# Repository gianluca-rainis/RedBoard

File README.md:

# Redboard
Design an RP2040-powered board, get funds to build it!

## What is Readboard
Redboard is a YSWS where students design a custom RP2040-powered PCB from scratch, earn credits based on tracked hours, and redeem them for grants to manufacture and build their board.

## How does it works
For each project there will be two phases: 
- The design phase, where participants design any RP2040-powered board, develop the PCB and track their time spent on KiCad with Lapse. After shipping the project, they will receive 1 credit per hour tracked. 
- The build phase, where participants spend their credits in the shop to get: a PCB manufacturing grant; a components grant; optional tools (soldering iron, multimeter, etc.). Then they physically build the board, tracking the build time with Lapse and earning additional credits.

## What a shipped project will have
A shipped Phase 1 project includes:
- Public GitHub repo with all the source files
- Handwritten README and JOURNEY files
- Photos of the board design

A shipped Phase 2 project includes:
- A short video of the board working
- Photos of the assembled board

## Colors
#c01749
#d42060
#e01f5a

## Env file content
> SITE_URL

The url of the site

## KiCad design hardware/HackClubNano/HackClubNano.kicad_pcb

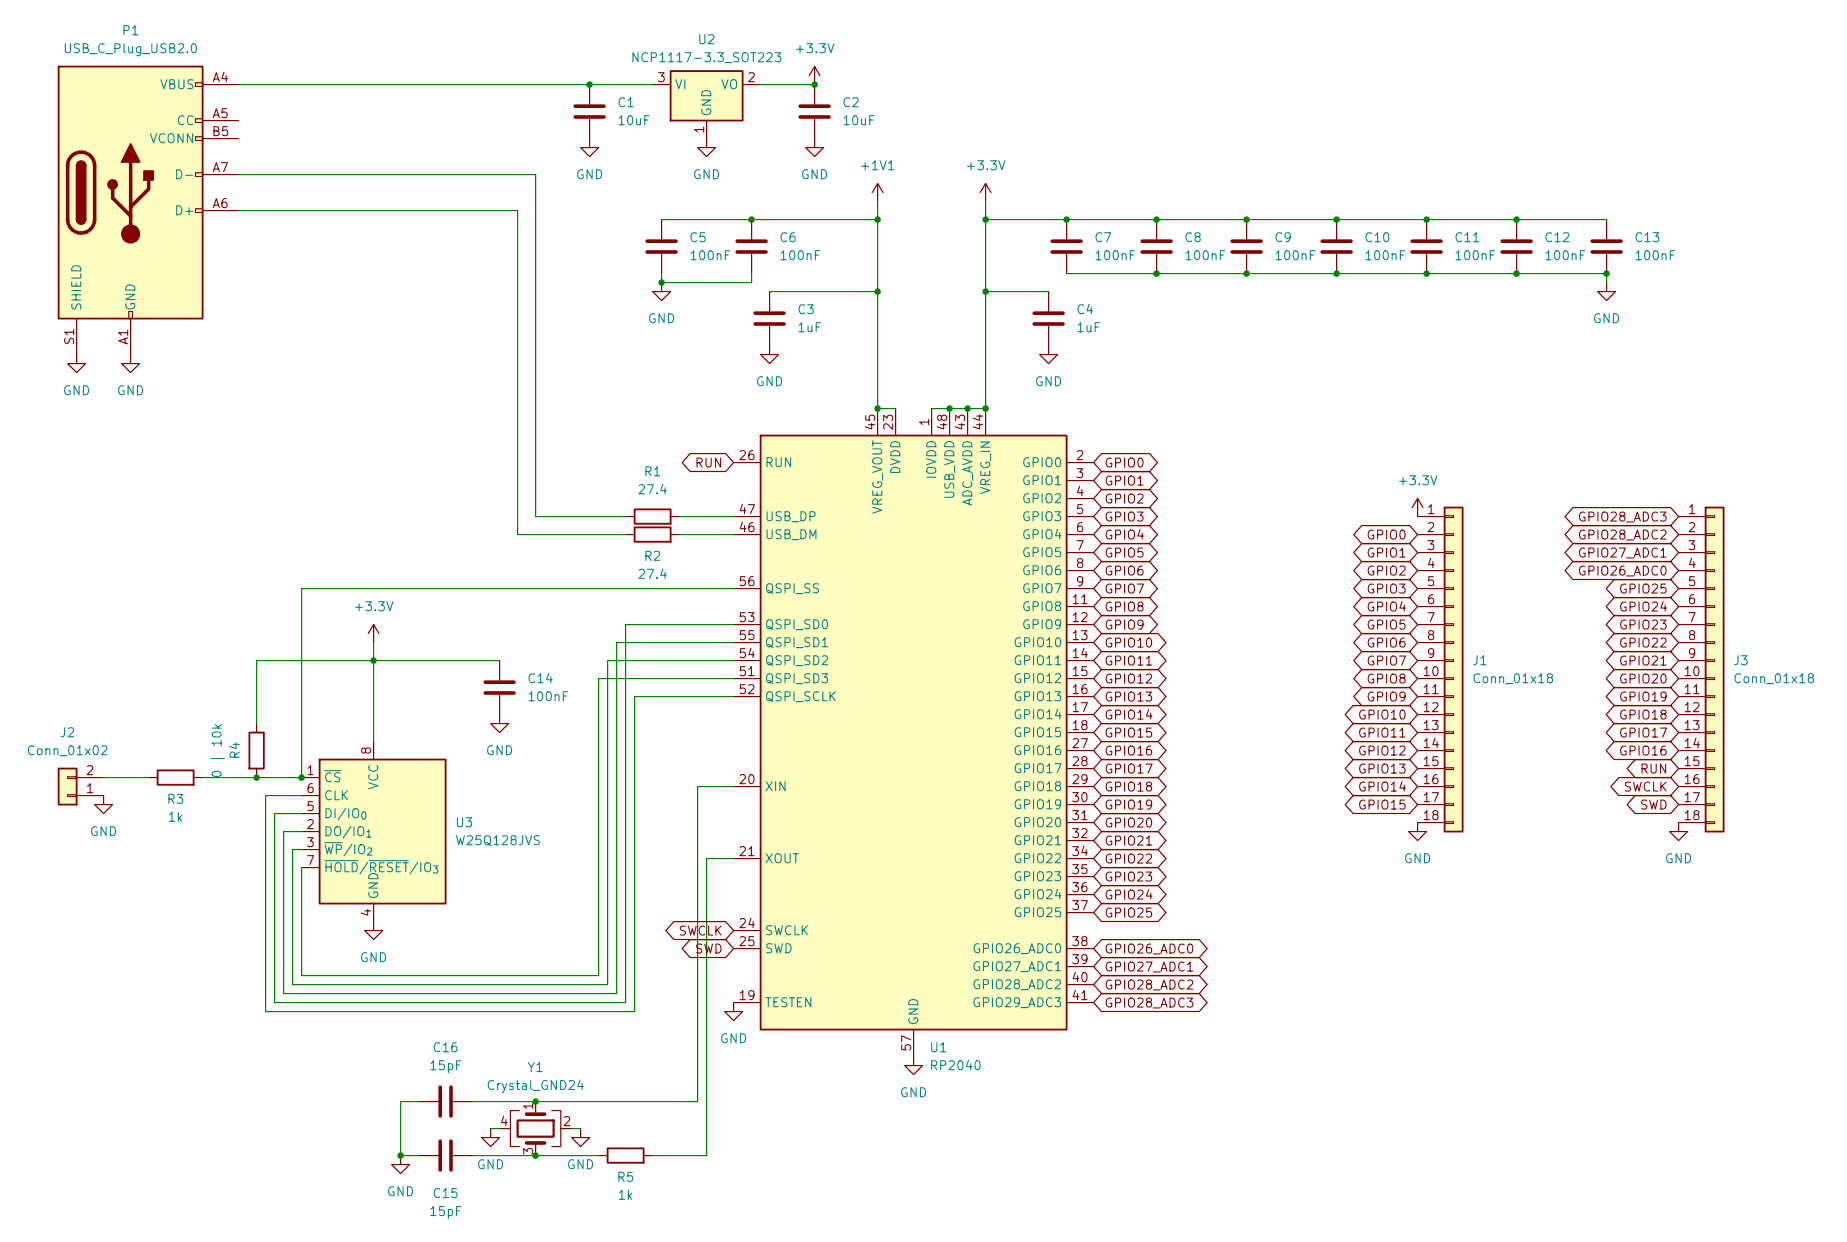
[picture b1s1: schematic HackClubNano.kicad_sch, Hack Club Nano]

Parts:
C1, C2: 10uF; C_0603_1608Metric
C3, C4: 1uF; C_0603_1608Metric
C5, C6, C7, C8, C9, C10, C11, C12, C13, C14: 100nF; C_0603_1608Metric
C15, C16: 15pF; C_0603_1608Metric
J1, J3: Conn_01x18; PinHeader_1x18_P2.00mm_Vertical
J2: Conn_01x02; PinHeader_1x02_P2.00mm_Vertical
P1: USB_C_Plug_USB2.0; USB_C_Receptacle_HRO_TYPE-C-31-M-12
R1, R2: 27.4; R_Axial_DIN0207_L6.3mm_D2.5mm_P7.62mm_Horizontal
R3, R5: 1k; R_Axial_DIN0207_L6.3mm_D2.5mm_P7.62mm_Horizontal
R4: 0 | 10k; R_Axial_DIN0207_L6.3mm_D2.5mm_P7.62mm_Horizontal
U1: RP2040; QFN-56-1EP_7x7mm_P0.4mm_EP3.2x3.2mm
U2: NCP1117-3.3_SOT223; SOT-223-3_TabPin2
U3: W25Q128JVS; SOIC-8_5.3x5.3mm_P1.27mm
Y1: Crystal_GND24; Crystal_SMD_5032-4Pin_5.0x3.2mm

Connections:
+1V1: C3.1, C5.1, C6.1, U1.23 (DVDD), U1.45 (VREG_VOUT), U1.50 (DVDD); also elsewhere on the board
+3.3V: C2.1, C4.1, C7.1, C8.1, C9.1, C10.1, C11.1, C12.1, C13.1, C14.1, J1.1, R4.1, U1.1 (IOVDD), U1.10 (IOVDD), U1.22 (IOVDD), U1.33 (IOVDD), U1.42 (IOVDD), U1.43 (ADC_AVDD), U1.44 (VREG_IN), U1.48 (USB_VDD), U1.49 (IOVDD), U2.2 (VO), U3.8 (VCC); also elsewhere on the board
GND: C1.2, C2.2, C3.2, C4.2, C5.2, C6.2, C7.2, C8.2, C9.2, C10.2, C11.2, C12.2, C13.2, C14.2, C15.2, C16.1, J1.18, J2.1, J3.18, P1.A1 (GND), P1.A12 (GND), P1.B1 (GND), P1.B12 (GND), P1.S1 (SHIELD), U1.19 (TESTEN), U1.57 (GND), U2.1 (GND), U3.4 (GND), Y1.2, Y1.4; also elsewhere on the board
GPIO0: J1.2, U1.2 (GPIO0); also elsewhere on the board
GPIO1: J1.3, U1.3 (GPIO1); also elsewhere on the board
GPIO2: J1.4, U1.4 (GPIO2); also elsewhere on the board
GPIO3: J1.5, U1.5 (GPIO3); also elsewhere on the board
GPIO4: J1.6, U1.6 (GPIO4); also elsewhere on the board
GPIO5: J1.7, U1.7 (GPIO5); also elsewhere on the board
GPIO6: J1.8, U1.8 (GPIO6); also elsewhere on the board
GPIO7: J1.9, U1.9 (GPIO7); also elsewhere on the board
GPIO8: J1.10, U1.11 (GPIO8); also elsewhere on the board
GPIO9: J1.11, U1.12 (GPIO9); also elsewhere on the board
GPIO10: J1.12, U1.13 (GPIO10); also elsewhere on the board
GPIO11: J1.13, U1.14 (GPIO11); also elsewhere on the board
GPIO12: J1.14, U1.15 (GPIO12); also elsewhere on the board
GPIO13: J1.15, U1.16 (GPIO13); also elsewhere on the board
GPIO14: J1.16, U1.17 (GPIO14); also elsewhere on the board
GPIO15: J1.17, U1.18 (GPIO15); also elsewhere on the board
GPIO16: J3.14, U1.27 (GPIO16); also elsewhere on the board
GPIO17: J3.13, U1.28 (GPIO17); also elsewhere on the board
GPIO18: J3.12, U1.29 (GPIO18); also elsewhere on the board
GPIO19: J3.11, U1.30 (GPIO19); also elsewhere on the board
GPIO20: J3.10, U1.31 (GPIO20); also elsewhere on the board
GPIO21: J3.9, U1.32 (GPIO21); also elsewhere on the board
GPIO22: J3.8, U1.34 (GPIO22); also elsewhere on the board
GPIO23: J3.7, U1.35 (GPIO23); also elsewhere on the board
GPIO24: J3.6, U1.36 (GPIO24); also elsewhere on the board
GPIO25: J3.5, U1.37 (GPIO25); also elsewhere on the board
GPIO26_ADC0: J3.4, U1.38 (GPIO26_ADC0); also elsewhere on the board
GPIO27_ADC1: J3.3, U1.39 (GPIO27_ADC1); also elsewhere on the board
GPIO28_ADC2: J3.2, U1.40 (GPIO28_ADC2); also elsewhere on the board
GPIO28_ADC3: J3.1, U1.41 (GPIO29_ADC3); also elsewhere on the board
unnamed: C15.1, R5.1, Y1.3
unnamed: J2.2, R3.1
unnamed: P1.A6 (D+), R2.1
unnamed: P1.A7 (D-), R1.1
unnamed 37: U1.52 (QSPI_SCLK), U3.6 (CLK); also elsewhere on the board
unnamed 38: U1.53 (QSPI_SD0), U3.5 (DI/IO_{0}); also elsewhere on the board
unnamed 39: U1.55 (QSPI_SD1), U3.2 (DO/IO_{1}); also elsewhere on the board
unnamed 40: U1.54 (QSPI_SD2), U3.3 (~WP/IO_{2}); also elsewhere on the board
unnamed 41: U1.51 (QSPI_SD3), U3.7 (~HOLD/~RESET/IO_{3}); also elsewhere on the board
unnamed 42: R3.2, R4.2, U1.56 (QSPI_SS), U3.1 (~CS); also elsewhere on the board
unnamed 43: R2.2, U1.46 (USB_DM); also elsewhere on the board
unnamed 44: R1.2, U1.47 (USB_DP); also elsewhere on the board
unnamed 45: C16.2, U1.20 (XIN), Y1.1; also elsewhere on the board
unnamed 46: R5.2, U1.21 (XOUT); also elsewhere on the board
unnamed: C1.1, P1.A4 (VBUS), P1.A9 (VBUS), P1.B4 (VBUS), P1.B9 (VBUS), U2.3 (VI)
RUN: J3.15, U1.26 (RUN); also elsewhere on the board
SWCLK: J3.16, U1.24 (SWCLK); also elsewhere on the board
SWD: J3.17, U1.25 (SWD); also elsewhere on the board

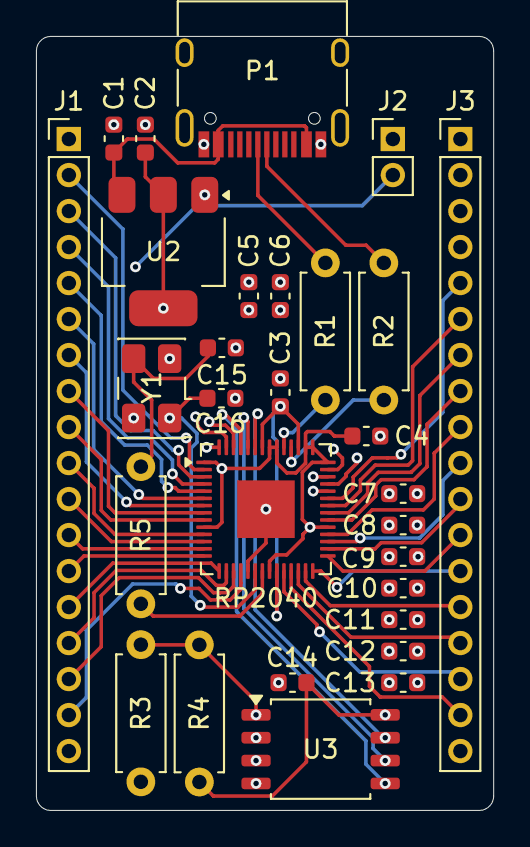
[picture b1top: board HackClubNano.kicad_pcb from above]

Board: 4 copper layers, 25.4 x 43.0 mm, 29 parts (0 on the bottom side), 51 nets.

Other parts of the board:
RP2040: RP2040; QFN-56-1EP_7x7mm_P0.4mm_EP3.2x3.2mm

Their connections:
+1V1: RP2040.23 (DVDD), RP2040.45 (VREG_VOUT), RP2040.50 (DVDD); also elsewhere on the board
+3.3V: RP2040.1 (IOVDD), RP2040.10 (IOVDD), RP2040.22 (IOVDD), RP2040.33 (IOVDD), RP2040.42 (IOVDD), RP2040.43 (ADC_AVDD), RP2040.44 (VREG_IN), RP2040.48 (USB_VDD), RP2040.49 (IOVDD); also elsewhere on the board
GND: RP2040.19 (TESTEN), RP2040.57 (GND); also elsewhere on the board
GPIO0: RP2040.2 (GPIO0); also elsewhere on the board
GPIO1: RP2040.3 (GPIO1); also elsewhere on the board
GPIO2: RP2040.4 (GPIO2); also elsewhere on the board
GPIO3: RP2040.5 (GPIO3); also elsewhere on the board
GPIO4: RP2040.6 (GPIO4); also elsewhere on the board
GPIO5: RP2040.7 (GPIO5); also elsewhere on the board
GPIO6: RP2040.8 (GPIO6); also elsewhere on the board
GPIO7: RP2040.9 (GPIO7); also elsewhere on the board
GPIO8: RP2040.11 (GPIO8); also elsewhere on the board
GPIO9: RP2040.12 (GPIO9); also elsewhere on the board
GPIO10: RP2040.13 (GPIO10); also elsewhere on the board
GPIO11: RP2040.14 (GPIO11); also elsewhere on the board
GPIO12: RP2040.15 (GPIO12); also elsewhere on the board
GPIO13: RP2040.16 (GPIO13); also elsewhere on the board
GPIO14: RP2040.17 (GPIO14); also elsewhere on the board
GPIO15: RP2040.18 (GPIO15); also elsewhere on the board
GPIO16: RP2040.27 (GPIO16); also elsewhere on the board
GPIO17: RP2040.28 (GPIO17); also elsewhere on the board
GPIO18: RP2040.29 (GPIO18); also elsewhere on the board
GPIO19: RP2040.30 (GPIO19); also elsewhere on the board
GPIO20: RP2040.31 (GPIO20); also elsewhere on the board
GPIO21: RP2040.32 (GPIO21); also elsewhere on the board
GPIO22: RP2040.34 (GPIO22); also elsewhere on the board
GPIO23: RP2040.35 (GPIO23); also elsewhere on the board
GPIO24: RP2040.36 (GPIO24); also elsewhere on the board
GPIO25: RP2040.37 (GPIO25); also elsewhere on the board
GPIO26_ADC0: RP2040.38 (GPIO26_ADC0); also elsewhere on the board
GPIO27_ADC1: RP2040.39 (GPIO27_ADC1); also elsewhere on the board
GPIO28_ADC2: RP2040.40 (GPIO28_ADC2); also elsewhere on the board
GPIO28_ADC3: RP2040.41 (GPIO29_ADC3); also elsewhere on the board
unnamed 37: RP2040.52 (QSPI_SCLK); also elsewhere on the board
unnamed 38: RP2040.53 (QSPI_SD0); also elsewhere on the board
unnamed 39: RP2040.55 (QSPI_SD1); also elsewhere on the board
unnamed 40: RP2040.54 (QSPI_SD2); also elsewhere on the board
unnamed 41: RP2040.51 (QSPI_SD3); also elsewhere on the board
unnamed 42: RP2040.56 (QSPI_SS); also elsewhere on the board
unnamed 43: RP2040.46 (USB_DM); also elsewhere on the board
unnamed 44: RP2040.47 (USB_DP); also elsewhere on the board
unnamed 45: RP2040.20 (XIN); also elsewhere on the board
unnamed 46: RP2040.21 (XOUT); also elsewhere on the board
RUN: RP2040.26 (RUN); also elsewhere on the board
SWCLK: RP2040.24 (SWCLK); also elsewhere on the board
SWD: RP2040.25 (SWD); also elsewhere on the board

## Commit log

2026-04-05 Cloned the Boot site. Modified the project to be for Redboard.
2026-04-05 Finished a first simple version of the site.
2026-04-05 Removed the dashboard empty page. Made the guide's page simpler.
2026-04-06 Converted the project from TS to JS.
2026-04-06 Made the traces for the background of the hero in the home.
2026-04-06 Added some links in the footer.
2026-04-06 Added boards images in hero.
2026-04-06 Fixed the images to made the animations not sincronized and the design lighter.
2026-04-06 Added references to the original projects for the images in the home.
2026-04-07 Made the images for the "How it works" section. Made the credits image.
2026-04-07 Fixed the how it works section.
2026-04-07 Updated the "what counts" and the faq sections.
2026-04-08 Fixed some bugs.
2026-04-08 Made the side pattern for the home page.
2026-04-08 Made the first steps of the tutorial for kicad.
2026-04-08 Continued the tutorial with the schematics info.
2026-04-08 Added the usb and the power guides.
2026-04-09 Made the tutorial for Lapse.
2026-04-09 Made the flash, the crystal and the io pins guides.
2026-04-09 Started the PCB tutorial.
2026-04-09 Finished the pcb guide. Finished the Hack Club Nano board.
2026-04-09 Finished the tutorial. Updated the home of the guides. Exported the gerber files.
2026-04-10 Improved the how it works section. Removed the useless hardware test.
2026-04-11 Fixed the how it works section for mobile.
2026-04-25 Migrated the home page from app to pages.
2026-04-25 Finished the home in pages.
2026-04-25 Finished the guides fix.
2026-04-25 Started the RSVP page. Created a simple session manager. Prepared the DB functions.
